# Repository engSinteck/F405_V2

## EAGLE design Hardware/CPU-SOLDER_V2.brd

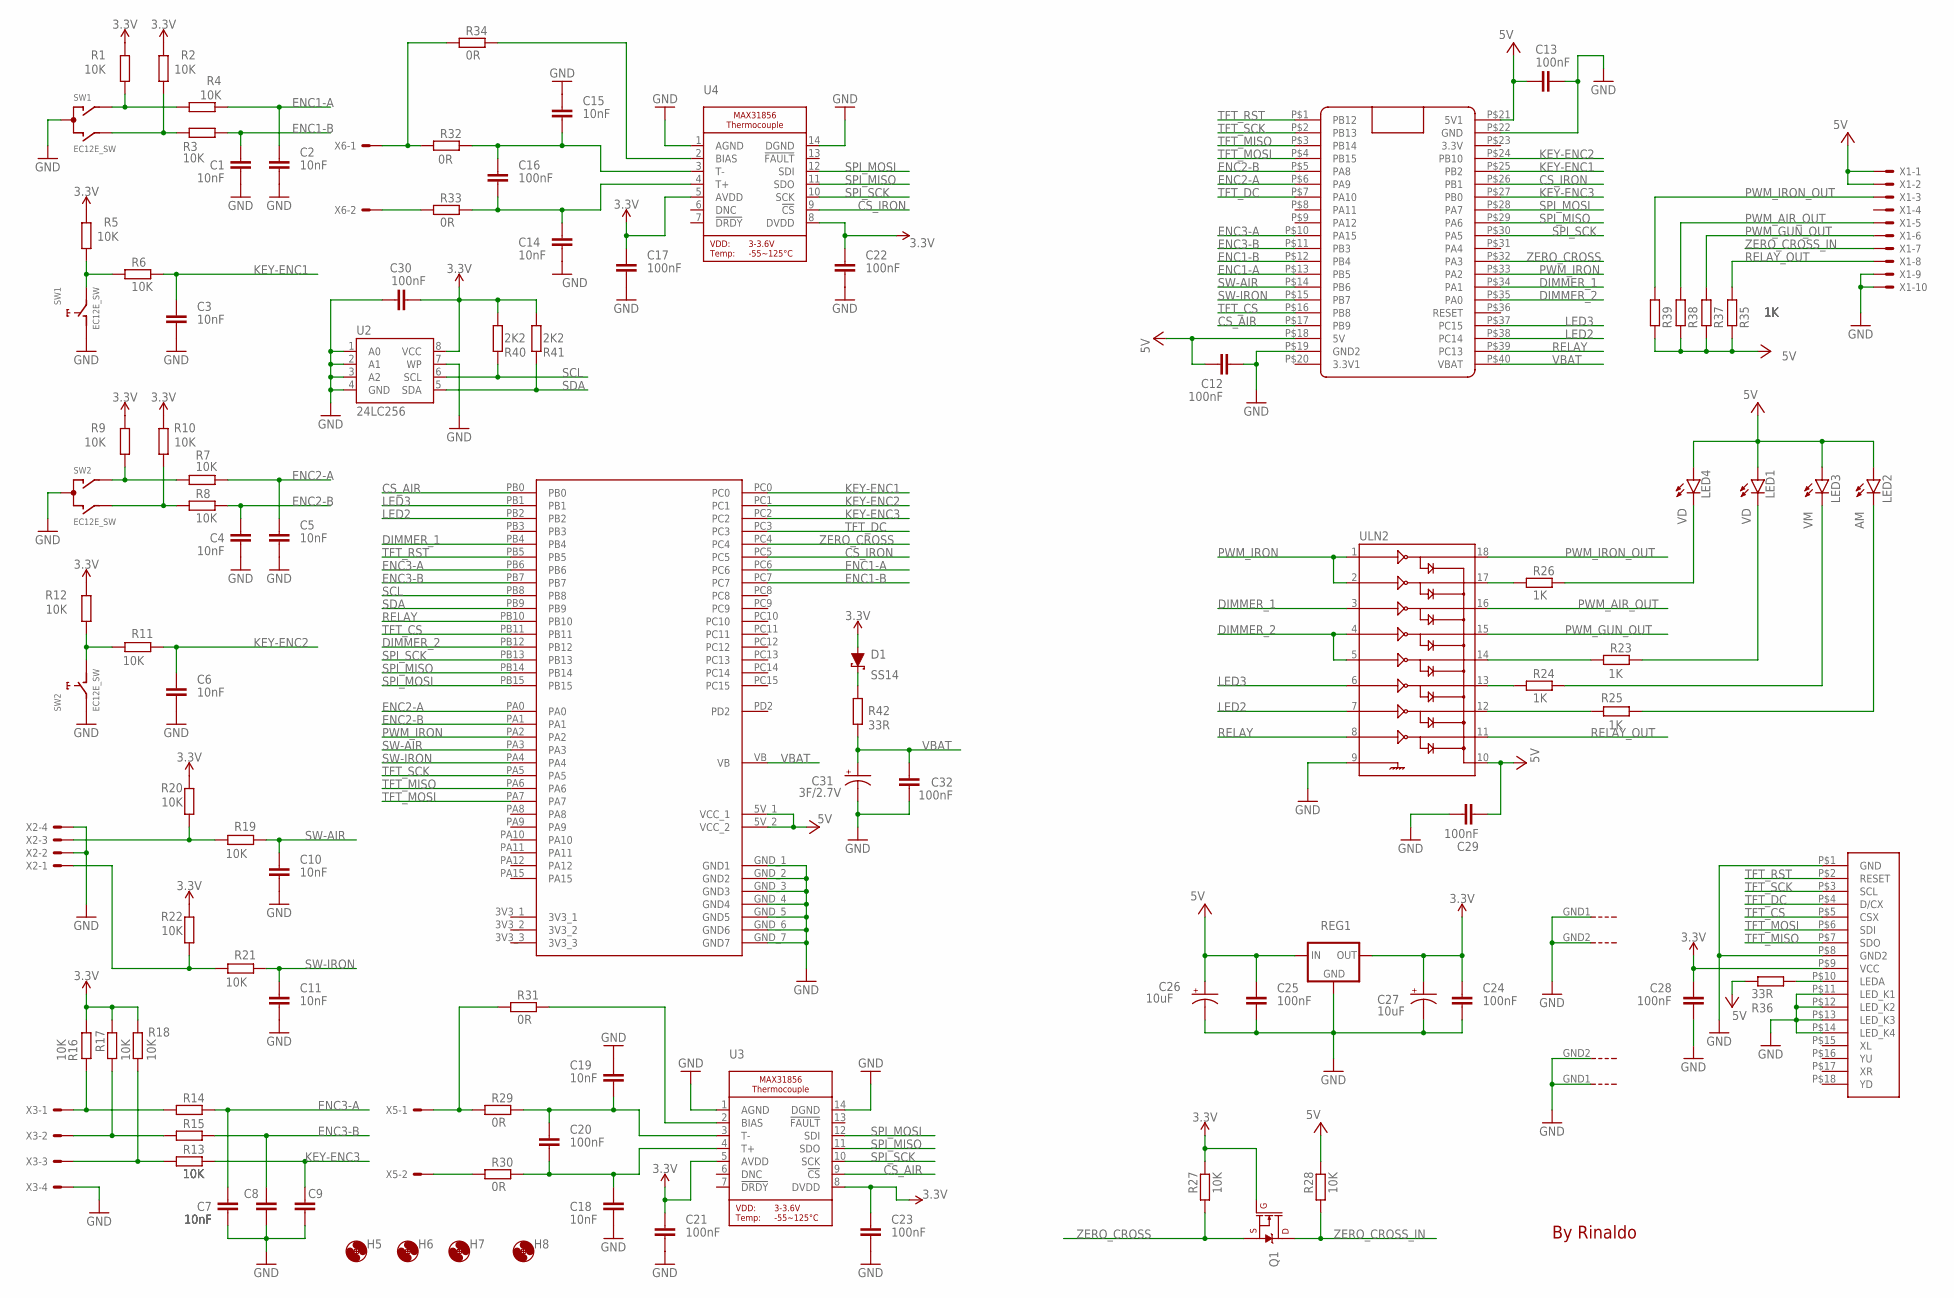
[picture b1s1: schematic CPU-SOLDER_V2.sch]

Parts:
C1, C2, C3, C4, C5, C6, C7, C8, C9, C10, C11, C14, C15, C18, C19: 10nF; C0603
C12, C13, C16, C17, C20, C21, C22, C23, C24, C25, C28, C29, C30, C32: 100nF; C0603
C26, C27: 10uF; EIA3528
C31: 3F/2.7V; CPOL-RADIAL-1F-2.7V
D1: SS14; SMA-DIODE
H5, H6, H7, H8: MOUNT-HOLE3.6; 3,6
LCD1: ILI9341-3.2
LED1, LED4: VD; LED5MM
LED2: AM; LED5MM
LED3: VM; LED5MM
Q1: 220mA/50V/3.5Ω; SOT23-3
R1, R2, R3, R4, R5, R6, R7, R8, R9, R10, R11, R12, R13, R14, R15, R16, R17, R18, R19, R20, R21, R22, R27, R28: 10K; R0603
R23, R24, R25, R26, R35, R37, R38, R39: 1K; R0603
R29, R30, R31, R32, R33, R34: 0R; R0603
R36, R42: 33R; R2512
R40, R41: 2K2; R0603
REG1: V_REG_LD1117VXXLD1117-SMD; SOT223
SW1, SW2: EC12E_SW; ALPS_EC12E_SW
U1: STM32-F411; BLACK-PILL-STM32_BLUE_PILL
U2: 24LC256; SO08
U3, U4: MICROBUILDER_MAX31856; MICROBUILDER_TSSOP14
U5: F405_WEACT
ULN2: ULN2803SOICW; SO18L
X1: JST-XH-10-PIN-ROUND-PAD; JST-XH-10-PACKAGE-ROUND-PAD
X2, X3: JST-XH-04-PIN-ROUND-PAD; JST-XH-04-PACKAGE-ROUND-PAD
X5, X6: JST-XH-02-PIN-ROUND-PAD; JST-XH-02-PACKAGE-ROUND-PAD

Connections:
3.3V: C17.2, C21.2, C22.2, C23.2, C24.2, C27.A (+), C28.2, C30.1, D1.A, LCD1.P$9 (VCC), Q1.1 (G), R1.2, R2.2, R5.2, R9.2, R10.2, R12.2, R16.2, R17.2, R18.2, R20.2, R22.2, R27.2, R40.1, R41.1, REG1.2 (OUT), U2.8 (VCC), U3.5 (AVDD), U3.8 (DVDD), U4.5 (AVDD), U4.8 (DVDD)
CS_AIR: U1.P$17 (PB9), U3.9 (!CS), U5.PB0
CS_IRON: U1.P$26 (PB1), U4.9 (!CS), U5.PC5
DIMMER_1: U1.P$34 (PA1), U5.PB4, ULN2.3
DIMMER_2: U1.P$35 (PA0), U5.PB12, ULN2.4, ULN2.5
ENC1-A: C2.1, R3.1, U1.P$13 (PB5), U5.PC6
ENC1-B: C1.1, R4.2, U1.P$12 (PB4), U5.PC7
ENC2-A: C5.1, R7.2, U1.P$6 (PA9), U5.PA0
ENC2-B: C4.1, R8.2, U1.P$5 (PA8), U5.PA1
ENC3-A: C7.1, R14.2, U1.P$10 (PA15), U5.PB6
ENC3-B: C8.1, R15.2, U1.P$11 (PB3), U5.PB7
GND: C1.2, C2.2, C3.2, C4.2, C5.2, C6.2, C7.2, C8.2, C9.2, C10.2, C11.2, C12.2, C13.2, C14.1, C15.2, C17.1, C18.1, C19.2, C21.1, C22.1, C23.1, C24.1, C25.1, C26.C (-), C27.C (-), C28.1, C29.2, C30.2, C31.-, C32.2, LCD1.P$1 (GND), LCD1.P$8 (GND2), LCD1.P$11 (LED_K1), LCD1.P$12 (LED_K2), LCD1.P$13 (LED_K3), LCD1.P$14 (LED_K4), REG1.1 (GND), SW1.C, SW1.D (1), SW1.GND1 (G), SW1.GND2 (G), SW2.C, SW2.E (2), SW2.GND1 (G), SW2.GND2 (G), U1.P$19 (GND2), U1.P$22 (GND), U2.1 (A0), U2.2 (A1), U2.3 (A2), U2.4 (GND), U2.7 (WP), U3.1 (AGND), U3.14 (DGND), U4.1 (AGND), U4.14 (DGND), U5.GND_1 (GND1), U5.GND_2 (GND2), U5.GND_3 (GND3), U5.GND_4 (GND4), U5.GND_5 (GND5), U5.GND_6 (GND6), U5.GND_7 (GND7), ULN2.9, X1.9, X1.10, X2.2, X2.4, X3.4
KEY-ENC1: C3.1, R6.1, U1.P$25 (PB2), U5.PC0
KEY-ENC2: C6.1, R11.1, U1.P$24 (PB10), U5.PC1
KEY-ENC3: C9.1, R13.2, U1.P$27 (PB0), U5.PC2
LED2: U1.P$38 (PC14), U5.PB2, ULN2.7
LED3: U1.P$37 (PC15), U5.PB1, ULN2.6
unnamed: R1.1, R3.2, SW1.A
unnamed: R2.1, R4.1, SW1.B
unnamed: R7.1, R9.1, SW2.A
unnamed: R8.1, R10.1, SW2.B
unnamed: R5.1, R6.2, SW1.E (2)
unnamed: R11.2, R12.1, SW2.D (1)
unnamed: R24.2, ULN2.13
unnamed: R14.1, R16.1, X3.1
unnamed: R15.1, R17.1, X3.2
unnamed: R13.1, R18.1, X3.3
unnamed: R25.1, ULN2.12
unnamed: R23.2, ULN2.14
unnamed: LED1.K (C), R23.1
unnamed: R21.2, R22.1, X2.1
unnamed: R19.2, R20.1, X2.3
unnamed: LED3.K (C), R24.1
unnamed: LED2.K (C), R25.2
unnamed: R26.1, ULN2.17
unnamed: LED4.K (C), R26.2
unnamed: R29.2, R31.2, X5.1
unnamed: R32.2, R34.2, X6.1
unnamed: LCD1.P$10 (LEDA), R36.2
unnamed: D1.C, R42.2
unnamed: C15.1, C16.2, R32.1, U4.3 (T-)
unnamed: C14.2, C16.1, R33.1, U4.4 (T+)
unnamed: R33.2, X6.2
unnamed: R34.1, U4.2 (BIAS)
unnamed: C19.1, C20.2, R29.1, U3.3 (T-)
unnamed: C18.2, C20.1, R30.1, U3.4 (T+)
unnamed: R30.2, X5.2
unnamed: R31.1, U3.2 (BIAS)
PWM_AIR_OUT: R38.1, ULN2.16, X1.5
PWM_GUN_OUT: R37.1, ULN2.15, X1.6
PWM_IRON: U1.P$33 (PA2), U5.PA2, ULN2.1, ULN2.2
PWM_IRON_OUT: R39.1, ULN2.18, X1.3
RELAY: U1.P$39 (PC13), U5.PB10, ULN2.8
RELAY_OUT: R35.1, ULN2.11, X1.8
SCL: R40.2, U2.6 (SCL), U5.PB8
SDA: R41.2, U2.5 (SDA), U5.PB9
SPI_MISO: U1.P$29 (PA6), U3.11 (SDO), U4.11 (SDO), U5.PB14
SPI_MOSI: U1.P$28 (PA7), U3.12 (SDI), U4.12 (SDI), U5.PB15
SPI_SCK: U1.P$30 (PA5), U3.10 (SCK), U4.10 (SCK), U5.PB13
SW-AIR: C10.1, R19.1, U1.P$14 (PB6), U5.PA3
SW-IRON: C11.1, R21.1, U1.P$15 (PB7), U5.PA4
TFT_CS: LCD1.P$5 (CSX), U1.P$16 (PB8), U5.PB11
TFT_DC: LCD1.P$4 (D/CX), U1.P$7 (PA10), U5.PC3
TFT_MISO: LCD1.P$7 (SDO), U1.P$3 (PB14), U5.PA6
TFT_MOSI: LCD1.P$6 (SDI), U1.P$4 (PB15), U5.PA7
TFT_RST: LCD1.P$2 (RESET), U1.P$1 (PB12), U5.PB5
TFT_SCK: LCD1.P$3 (SCL), U1.P$2 (PB13), U5.PA5
VBAT: C31.+, C32.1, R42.1, U1.P$40 (VBAT), U5.VB
VCC: C12.1, C13.1, C25.2, C26.A (+), C29.1, LED1.A, LED2.A, LED3.A, LED4.A, R28.2, R35.2, R36.1, R37.2, R38.2, R39.2, REG1.3 (IN), U1.P$18 (5V), U1.P$21 (5V1), U5.5V_1 (VCC_1), U5.5V_2 (VCC_2), ULN2.10, X1.1, X1.2
ZERO_CROSS: Q1.2 (S), R27.1, U1.P$32 (PA3), U5.PC4
ZERO_CROSS_IN: Q1.3 (D), R28.1, X1.7

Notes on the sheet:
By Rinaldo

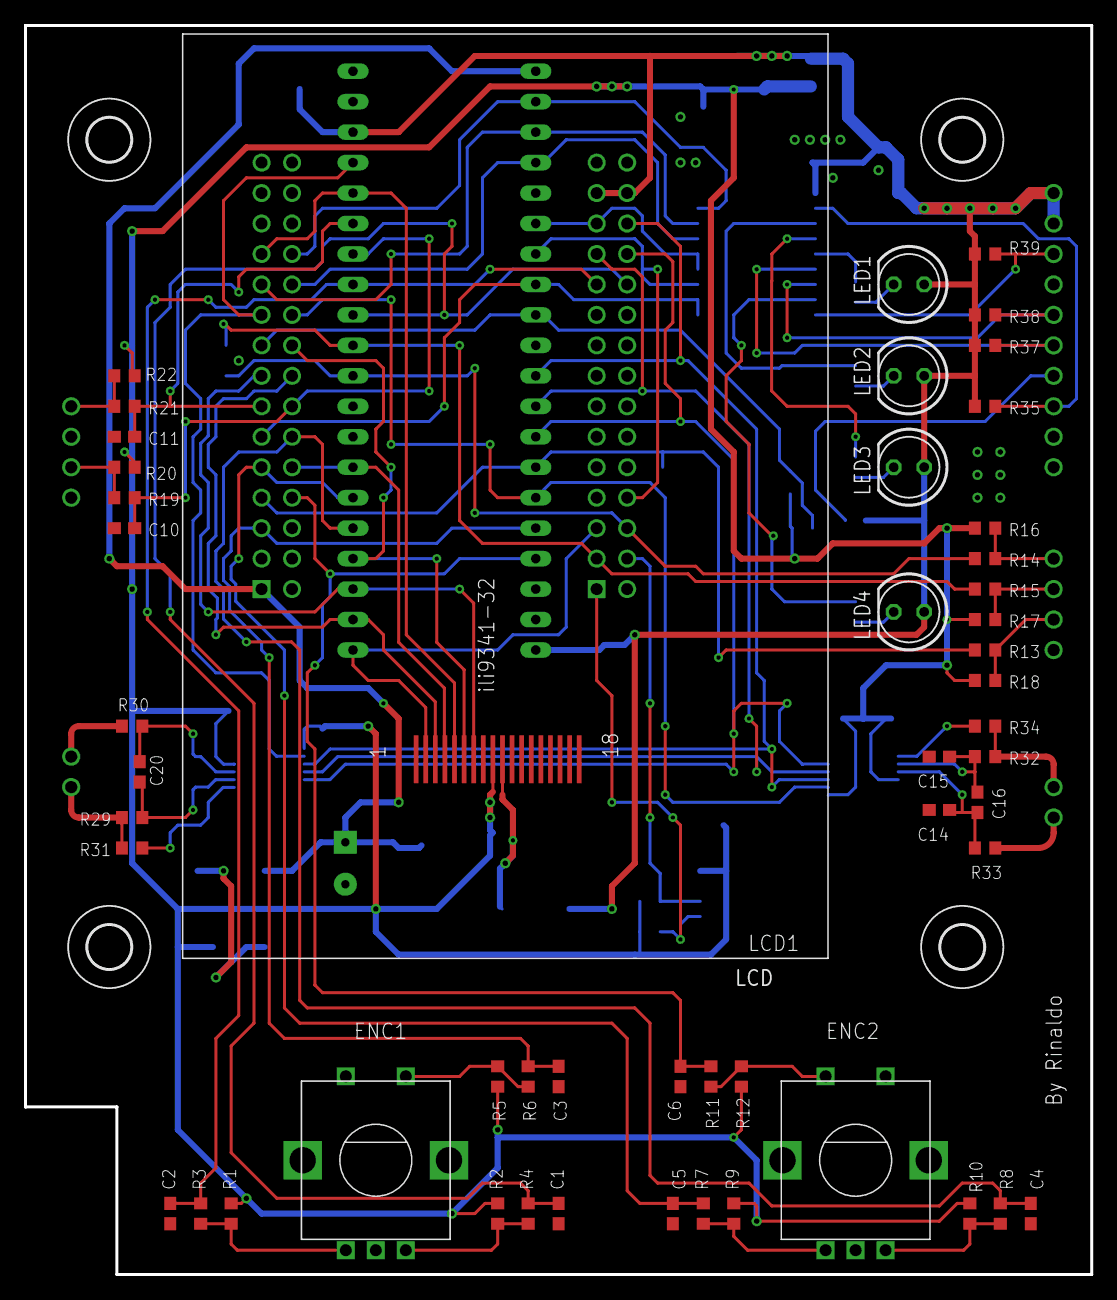
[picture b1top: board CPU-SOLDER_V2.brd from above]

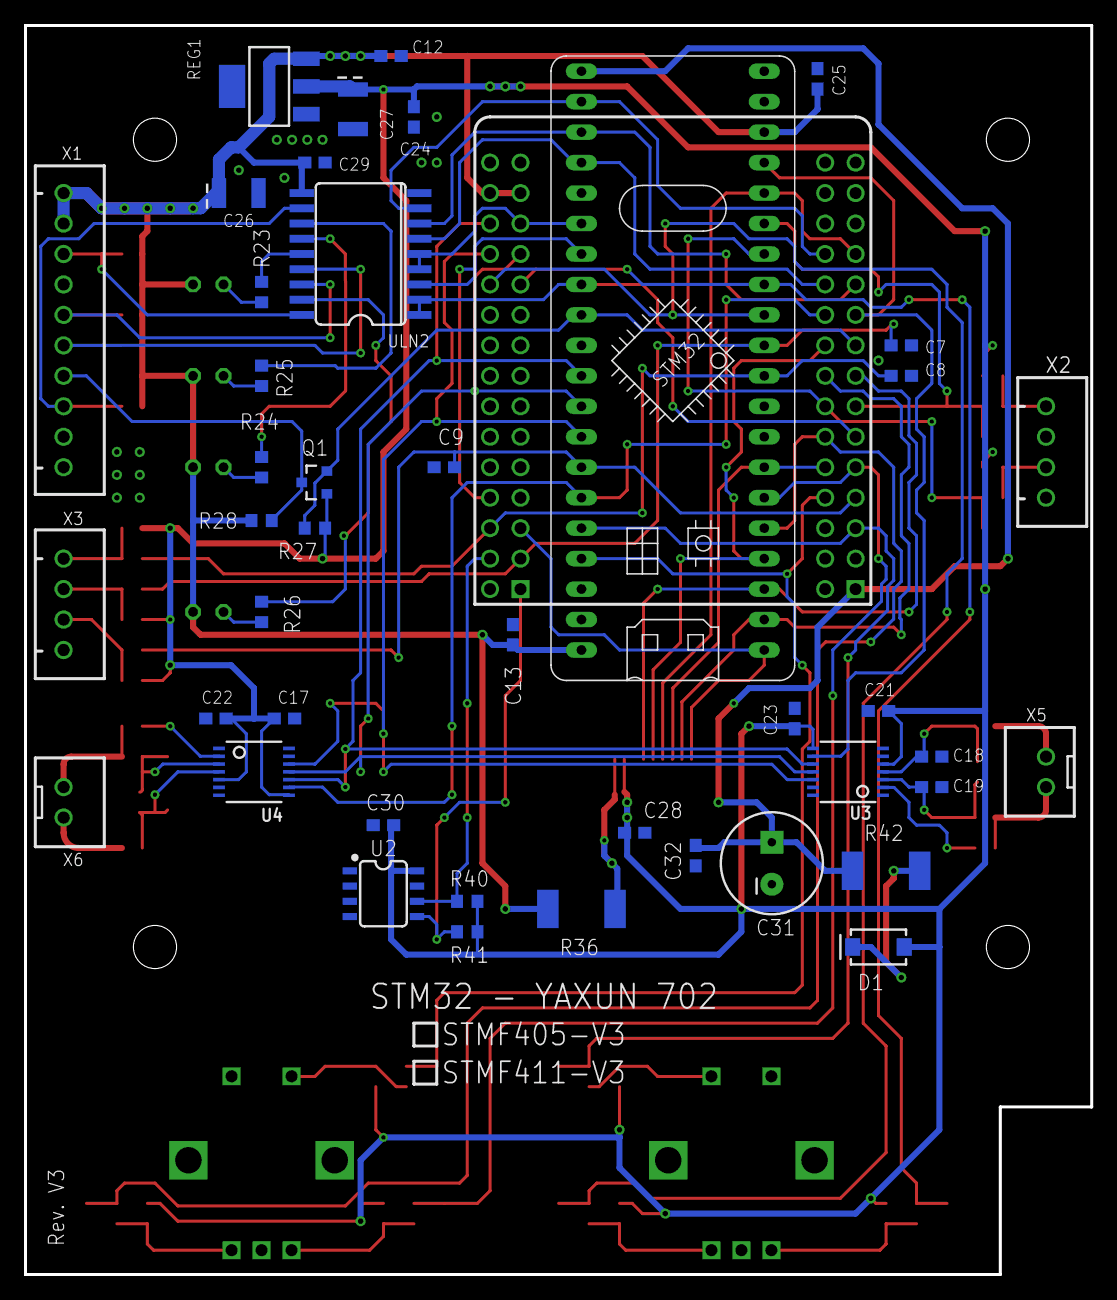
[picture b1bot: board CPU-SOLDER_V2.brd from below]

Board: 2 copper layers, 88.9 x 104.1 mm, 99 parts (44 on the bottom side), 71 nets.

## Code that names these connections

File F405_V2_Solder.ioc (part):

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Mcu.Name=STM32F405RGTx
Mcu.Package=LQFP64
Mcu.UserName=STM32F405RGTx
PA0-WKUP.GPIOParameters=GPIO_Label
PA0-WKUP.GPIO_Label=ENC2-A
PA0-WKUP.Signal=S_TIM2_CH1_ETR
PA1.GPIOParameters=GPIO_Label
PA1.GPIO_Label=ENC2-B
PA1.Signal=S_TIM2_CH2
PA10.Mode=Asynchronous
PA10.Signal=USART1_RX
PA11.Mode=Device_Only
PA11.Signal=USB_OTG_FS_DM
PA12.Mode=Device_Only
PA12.Signal=USB_OTG_FS_DP
PA13.Mode=Trace_Asynchronous_SW
PA13.Signal=SYS_JTMS-SWDIO
PA14.Mode=Trace_Asynchronous_SW
PA14.Signal=SYS_JTCK-SWCLK
PA15.GPIOParameters=GPIO_Label
PA15.GPIO_Label=TEST_120Hz
PA15.Signal=GPIO_Output
PA2.GPIOParameters=GPIO_Label
PA2.GPIO_Label=PWM_IRON
PA2.Signal=S_TIM9_CH1
PA3.GPIOParameters=GPIO_Label
PA3.GPIO_Label=SW_AIR
PA3.Signal=GPIO_Input
PA4.GPIOParameters=GPIO_Label
PA4.GPIO_Label=SW-IRON
PA4.Signal=GPIO_Input
PA5.GPIOParameters=GPIO_Label
PA5.GPIO_Label=TFT_SCK
PA5.Mode=Full_Duplex_Master
PA5.Signal=SPI1_SCK
PA6.GPIOParameters=GPIO_Label
PA6.GPIO_Label=TFT_MISO
PA6.Mode=Full_Duplex_Master
PA6.Signal=SPI1_MISO
PA7.GPIOParameters=GPIO_Label
PA7.GPIO_Label=TFT_MOSI
PA7.Mode=Full_Duplex_Master
PA7.Signal=SPI1_MOSI
PA8.GPIOParameters=GPIO_PuPd,GPIO_Label
PA8.GPIO_Label=SD_DETECT
PA8.GPIO_PuPd=GPIO_PULLUP
PA8.Signal=GPIO_Input
PA9.Mode=Asynchronous
PA9.Signal=USART1_TX
PB0.GPIOParameters=PinState,GPIO_Label
PB0.GPIO_Label=CS_GUN
PB0.PinState=GPIO_PIN_SET
PB0.Signal=GPIO_Output
PB1.GPIOParameters=GPIO_Label
PB1.GPIO_Label=LED3
PB1.Signal=GPIO_Output
PB10.GPIOParameters=PinState,GPIO_Label
PB10.GPIO_Label=RELAY
PB10.PinState=GPIO_PIN_SET
PB10.Signal=GPIO_Output
PB11.GPIOParameters=PinState,GPIO_Label
PB11.GPIO_Label=TFT_CS
PB11.PinState=GPIO_PIN_SET
PB11.Signal=GPIO_Output
PB12.GPIOParameters=PinState,GPIO_Label
PB12.GPIO_Label=DIMMER_2
PB12.PinState=GPIO_PIN_SET
PB12.Signal=GPIO_Output
PB13.GPIOParameters=GPIO_Label
PB13.GPIO_Label=SPI_SCK
PB13.Mode=Full_Duplex_Master
PB13.Signal=SPI2_SCK
PB14.GPIOParameters=GPIO_Label
PB14.GPIO_Label=SPI_MISO
PB14.Mode=Full_Duplex_Master
PB14.Signal=SPI2_MISO
PB15.GPIOParameters=GPIO_Label
PB15.GPIO_Label=SPI_MOSI
PB15.Mode=Full_Duplex_Master
PB15.Signal=SPI2_MOSI
PB2.GPIOParameters=GPIO_Label
PB2.GPIO_Label=LED2
PB2.Signal=GPIO_Output
PB3.Mode=Trace_Asynchronous_SW
PB3.Signal=SYS_JTDO-SWO
PB4.GPIOParameters=PinState,GPIO_Label
PB4.GPIO_Label=DIMMER_1
PB4.PinState=GPIO_PIN_SET
PB4.Signal=GPIO_Output
PB5.GPIOParameters=PinState,GPIO_Label
PB5.GPIO_Label=TFT_RST
PB5.PinState=GPIO_PIN_SET
PB5.Signal=GPIO_Output
PB6.GPIOParameters=GPIO_Label
PB6.GPIO_Label=ENC3-A
PB6.Signal=S_TIM4_CH1
PB7.GPIOParameters=GPIO_Label
PB7.GPIO_Label=ENC3-B
PB7.Signal=S_TIM4_CH2
PB8.Mode=I2C
PB8.Signal=I2C1_SCL
PB9.Mode=I2C
PB9.Signal=I2C1_SDA
PC0.GPIOParameters=GPIO_Label
PC0.GPIO_Label=KEY-ENC1
PC0.Signal=GPIO_Input
PC1.GPIOParameters=GPIO_Label
PC1.GPIO_Label=KEY-ENC2
PC1.Signal=GPIO_Input
PC10.Mode=SD_4_bits_Wide_bus
PC10.Signal=SDIO_D2
PC11.Mode=SD_4_bits_Wide_bus
PC11.Signal=SDIO_D3
PC12.Mode=SD_4_bits_Wide_bus
PC12.Signal=SDIO_CK
PC13-ANTI_TAMP.GPIOParameters=GPIO_PuPd,GPIO_Label
PC13-ANTI_TAMP.GPIO_Label=KEY_USER
PC13-ANTI_TAMP.GPIO_PuPd=GPIO_PULLDOWN
PC13-ANTI_TAMP.Signal=GPIO_Input
PC14-OSC32_IN.Mode=LSE-External-Oscillator
PC14-OSC32_IN.Signal=RCC_OSC32_IN
PC15-OSC32_OUT.Mode=LSE-External-Oscillator
PC15-OSC32_OUT.Signal=RCC_OSC32_OUT
PC2.GPIOParameters=GPIO_Label
PC2.GPIO_Label=KEY-ENC3
PC2.Signal=GPIO_Input
PC3.GPIOParameters=PinState,GPIO_Label
PC3.GPIO_Label=TFT_DC
PC3.PinState=GPIO_PIN_SET
PC3.Signal=GPIO_Output
PC4.GPIOParameters=GPIO_Label
PC4.GPIO_Label=ZERO_CROSS
PC4.Signal=GPXTI4
PC5.GPIOParameters=PinState,GPIO_Label
PC5.GPIO_Label=CS_IRON
PC5.PinState=GPIO_PIN_SET
PC5.Signal=GPIO_Output
PC6.GPIOParameters=GPIO_Label
PC6.GPIO_Label=ENC1-A
PC6.Signal=S_TIM3_CH1
PC7.GPIOParameters=GPIO_Label
PC7.GPIO_Label=ENC1-B
PC7.Signal=S_TIM3_CH2
PC8.Mode=SD_4_bits_Wide_bus
PC8.Signal=SDIO_D0
PC9.Mode=SD_4_bits_Wide_bus
PC9.Signal=SDIO_D1
PD2.Mode=SD_4_bits_Wide_bus
PD2.Signal=SDIO_CMD
PH0-OSC_IN.Mode=HSE-External-Oscillator
PH0-OSC_IN.Signal=RCC_OSC_IN
PH1-OSC_OUT.Mode=HSE-External-Oscillator
PH1-OSC_OUT.Signal=RCC_OSC_OUT
RCC.HSE_VALUE=8000000
RCC.SYSCLKFreq_VALUE=168000000
RCC.SYSCLKSource=RCC_SYSCLKSOURCE_PLLCLK
board=custom

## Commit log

2023-11-13 Update Pastes
2023-11-13 LCD Init priority
2023-11-14 Fix Name ENC1
2023-11-14 fix typo
2023-11-23 Update IOC file
2023-11-23 Update lvgl
2023-12-12 Add Hardware files

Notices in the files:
parts and their libraries:
SparkFun-Capacitors: Licensing: Creative Commons ShareAlike 4.0 International - https://creativecommons.org/licenses/by-sa/4.0
